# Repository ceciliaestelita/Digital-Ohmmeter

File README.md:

# Digital-Ohmmeter

Measure the resistive value of an impedance and display it on an LCD screen

<div align="center">

</div>
<div align="center">
  Scheme of the electrical circuit    
</div>  
<br/>  

The NPN transistor holds the configuration of maintaing the current on the emissor the same as the sum of the colector and base:  

$$
Ie = Ic + Ib
$$

As the current on the base is very low, we can assume that the current that passes through the unknown resistance has the same value as the one that passes through R2 or R3.  

The circuit always starts with the reference resistance as R2, for a lower resistances range, which is used for the first calculation of the current of the circuit (I1):

$$
I1=Va0/R2
$$

That is then used in the upper part of the circuit:

$$
Vx = 5V - Va1
$$

$$
Rx = (5V-Va1)/I1
$$

The choice between R2 and R3 for the real measurement is then made by a commutation system that, based of the Rx calculated, estimates if Rx is int the range of low or high resistances. If it is a low resistance, the arduino sends a digital signal from d5, if it's high, sends a digital signal from d6.  
Those digital signals are the tensions needed to activate the LED inside the photomos, that closes the circuit (as a mosfet) and lets current flow through R2 (for Rx = lower resistances) or R3 (for Rx = higher resistances).  
By letting current flow, the new current is taken by the calculation of Rx, and a more precise measure is made.

This circuit is designed to work in a range of resistances between 200 Ohms and 20 kOhms with a 1% error rate.

<div align="center">
  
</div>  
<div align="center">
  Circuit on TinkerCad   
</div>  
<br/>

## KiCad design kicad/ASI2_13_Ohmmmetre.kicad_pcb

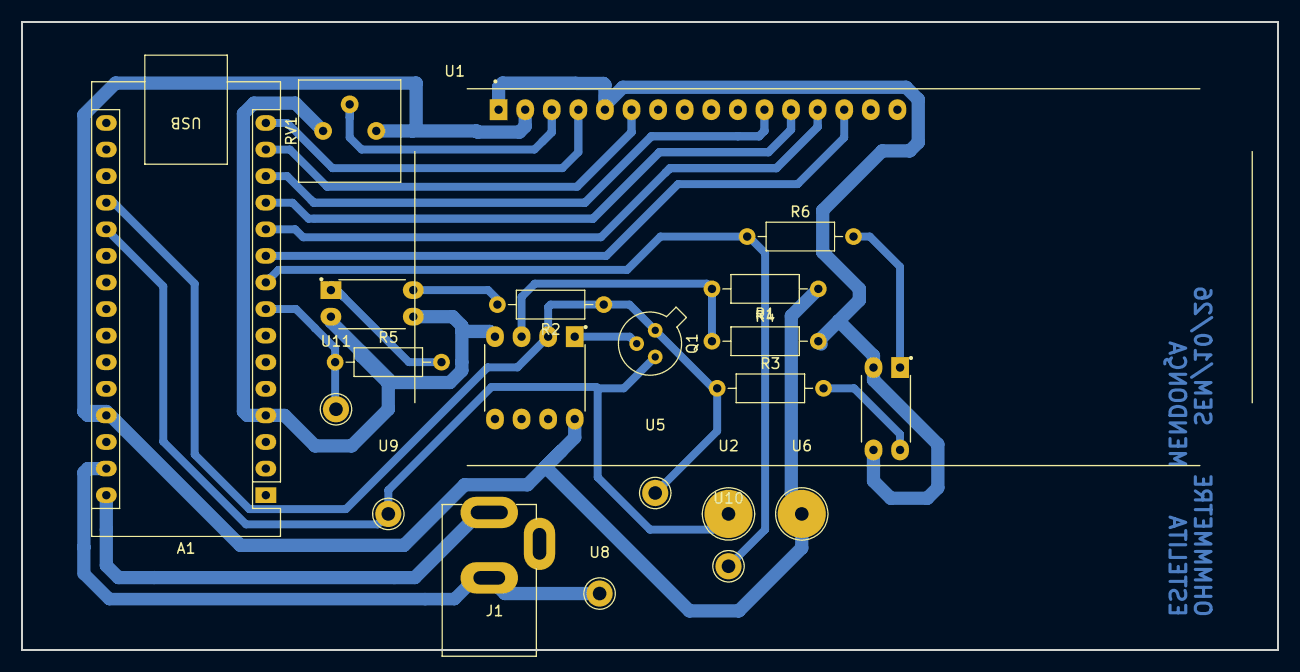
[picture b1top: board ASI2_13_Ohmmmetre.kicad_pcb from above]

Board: 2 copper layers, 120.0 x 60.0 mm, 21 parts (0 on the bottom side), 20 nets.

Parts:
A1: Arduino_Nano_v2.x; Arduino_Nano
J1: RAPC722X; SWITCHCRAFT_RAPC722X
Q1: 2N2219 - 2N2222; TO-18-ENSE3
R1, R2, R3, R4, R5, R6: R; Axial_4pas
RV1: R_Potentiometer; Pot_mono
U1: LCD2X16; LCD_LCD2X16
U2, U6: canon_insertion
U3, U4: AQY210EH; DIP4
U5, U8, U9, U10, U11: point_test
U7: MCP6282; DIP8

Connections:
+5V: A1.27 (+5V), R1.1, RV1.1, U1.2 (VDD), U6.1, U7.8 (V+)
+9V: A1.30 (VIN), J1.PIN
/DB4: A1.13 (D10), U1.11 (DB4)
/DB5: A1.12 (D9), U1.12 (DB5)
/DB6: A1.11 (D8), U1.13 (DB6)
/DB7: A1.10 (D7), U1.14 (DB7)
/E: A1.14 (D11), U1.6 (E)
/RS: A1.15 (D12), U1.4 (RS)
GND: A1.4 (GND), A1.29 (GND), J1.SLEEVE, R4.2, RV1.3, U1.1 (VSS), U1.5 (R/W), U3.2, U3.3, U4.2, U4.3, U7.4 (V-), U8.1
unnamed: Q1.1 (B), U7.1 (VoutA_)
unnamed: R2.2, U3.4
unnamed: R3.2, U4.4
unnamed: R5.2, U3.1
unnamed: R6.2, U4.1
unnamed: RV1.2, U1.3 (VO)
unnamed: R1.2, R4.1, U7.3 (A+)
a0: A1.19 (A0), Q1.3 (E), R2.1, R3.1, U5.1, U7.2 (A-)
a1: A1.20 (A1), Q1.2 (C), U2.1, U9.1
d5: A1.8 (D5), R5.1, U11.1
d6: A1.9 (D6), R6.1, U10.1
